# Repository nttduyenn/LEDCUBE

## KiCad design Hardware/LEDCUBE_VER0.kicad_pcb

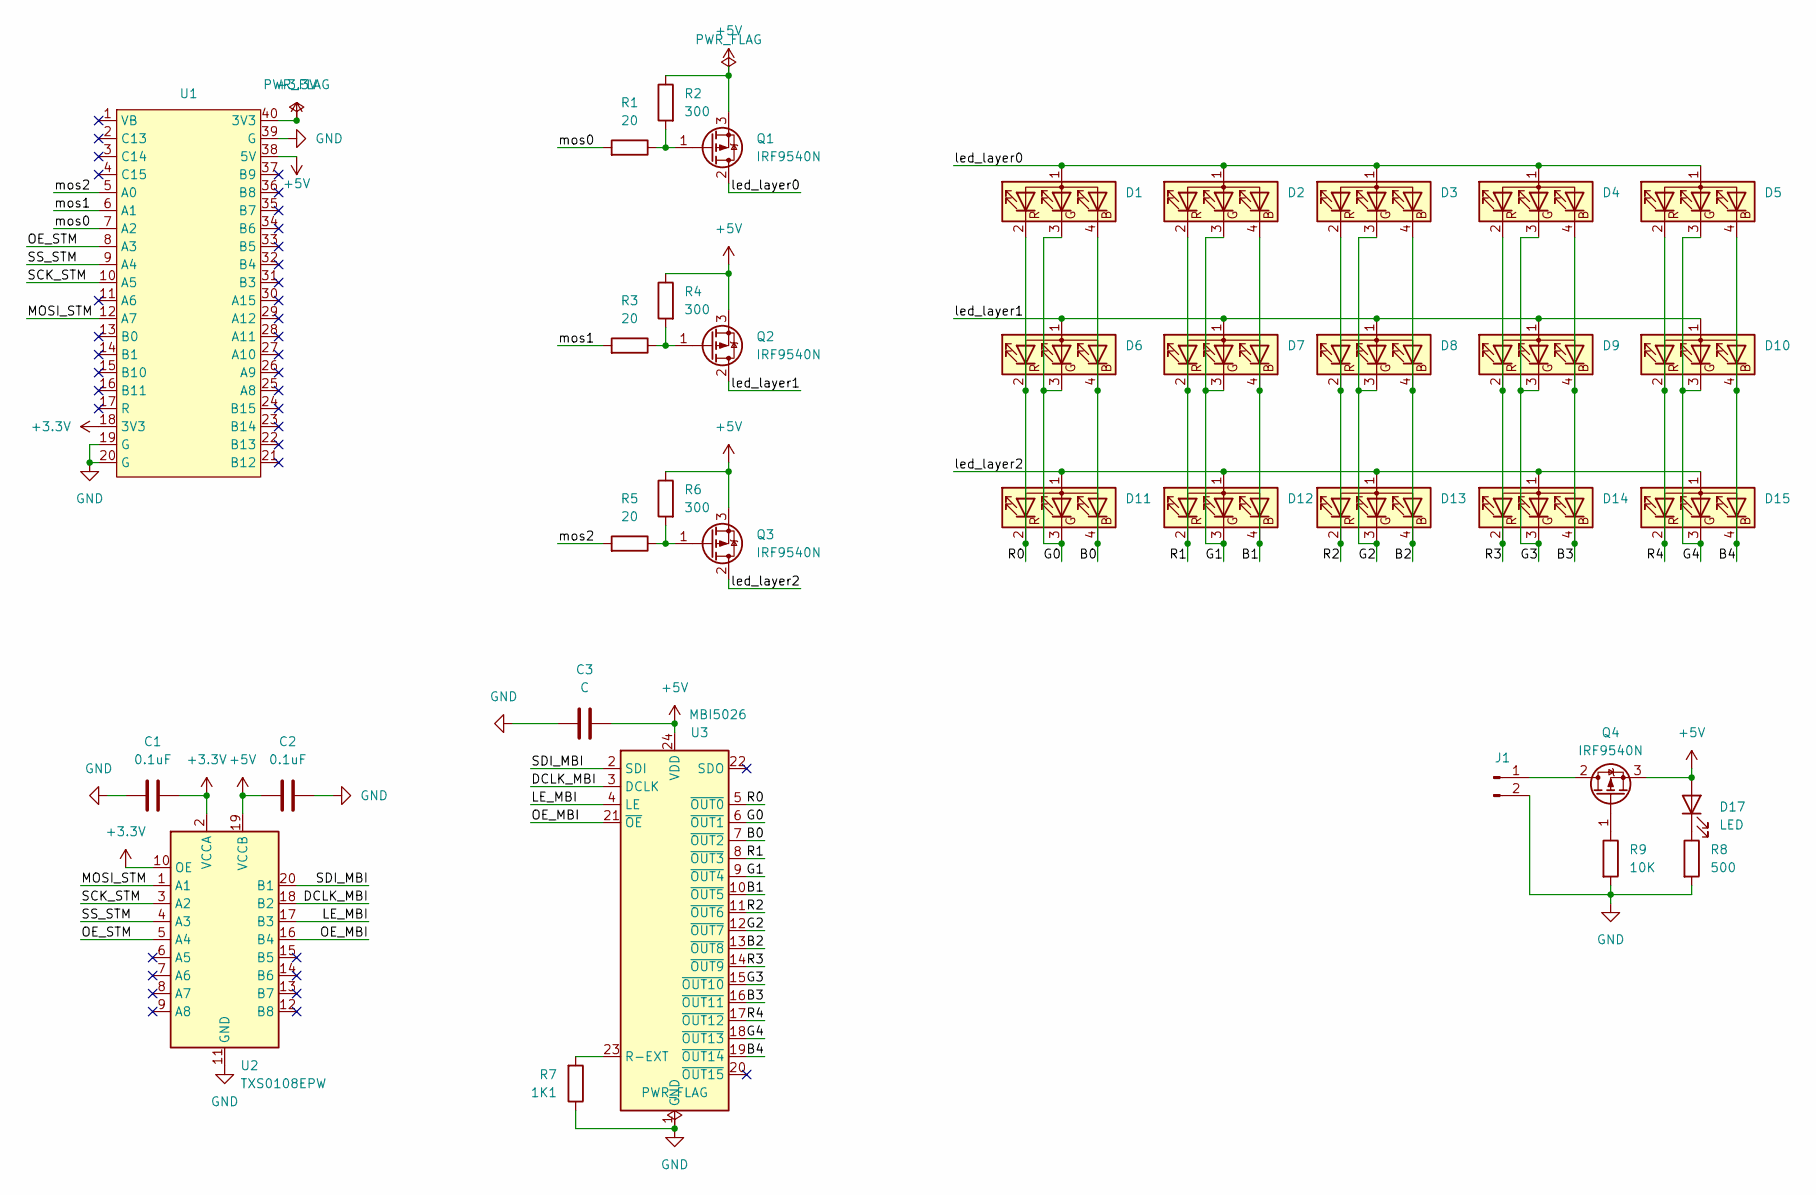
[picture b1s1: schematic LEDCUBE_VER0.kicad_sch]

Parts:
C1, C2: 0.1uF; C_0603_1608Metric_Pad1.08x0.95mm_HandSolder
C3: C; C_0805_2012Metric_Pad1.18x1.45mm_HandSolder
D1, D2, D3, D4, D5, D6, D7, D8, D9, D10, D11, D12, D13, D14, D15: LED_ARGB; LED_D5.0mm-4_RGB
D17: LED; D_0805_2012Metric_Pad1.15x1.40mm_HandSolder
J1: Conn_01x02_Pin; TerminalBlock_Phoenix_PT-1,5-2-5.0-H_1x02_P5.00mm_Horizontal
Q1, Q2, Q3, Q4: IRF9540N; TO-220-3_Vertical
R1, R3, R5: 20; R_0805_2012Metric_Pad1.20x1.40mm_HandSolder
R2, R4, R6: 300; R_0805_2012Metric_Pad1.20x1.40mm_HandSolder
R7: 1K1; R_0805_2012Metric_Pad1.20x1.40mm_HandSolder
R8: 500; D_0805_2012Metric_Pad1.15x1.40mm_HandSolder
R9: 10K; D_0805_2012Metric_Pad1.15x1.40mm_HandSolder
U1: STM32F1_BluePill
U2: TXS0108EPW; TSSOP-20_4.4x6.5mm_P0.65mm
U3: MBI5026; SOP-24

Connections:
+3.3V: C1.2, U1.18 (3V3), U1.40 (3V3), U2.2 (VCCA), U2.10 (OE)
+5V: C2.1, C3.2, D17.2 (A), Q1.3 (S), Q2.3 (S), Q3.3 (S), Q4.3 (S), R2.1, R4.1, R6.1, U1.38 (5V), U2.19 (VCCB), U3.24 (VDD)
/B0: D1.4 (BK), D6.4 (BK), D11.4 (BK), U3.7 (~OUT2)
/B1: D2.4 (BK), D7.4 (BK), D12.4 (BK), U3.10 (~OUT5)
/B2: D3.4 (BK), D8.4 (BK), D13.4 (BK), U3.13 (~OUT8)
/B3: D4.4 (BK), D9.4 (BK), D14.4 (BK), U3.16 (~OUT11)
/B4: D5.4 (BK), D10.4 (BK), D15.4 (BK), U3.19 (~OUT14)
/DCLK_MBI: U2.18 (B2), U3.3 (DCLK)
/G0: D1.3 (GK), D6.3 (GK), D11.3 (GK), U3.6 (~OUT1)
/G1: D2.3 (GK), D7.3 (GK), D12.3 (GK), U3.9 (~OUT4)
/G2: D3.3 (GK), D8.3 (GK), D13.3 (GK), U3.12 (~OUT7)
/G3: D4.3 (GK), D9.3 (GK), D14.3 (GK), U3.15 (~OUT10)
/G4: D5.3 (GK), D10.3 (GK), D15.3 (GK), U3.18 (~OUT13)
/LE_MBI: U2.17 (B3), U3.4 (LE)
/MOSI_STM: U1.12 (A7), U2.1 (A1)
/OE_MBI: U2.16 (B4), U3.21 (~OE)
/OE_STM: U1.8 (A3), U2.5 (A4)
/R0: D1.2 (RK), D6.2 (RK), D11.2 (RK), U3.5 (~OUT0)
/R1: D2.2 (RK), D7.2 (RK), D12.2 (RK), U3.8 (~OUT3)
/R2: D3.2 (RK), D8.2 (RK), D13.2 (RK), U3.11 (~OUT6)
/R3: D4.2 (RK), D9.2 (RK), D14.2 (RK), U3.14 (~OUT9)
/R4: D5.2 (RK), D10.2 (RK), D15.2 (RK), U3.17 (~OUT12)
/SCK_STM: U1.10 (A5), U2.3 (A2)
/SDI_MBI: U2.20 (B1), U3.2 (SDI)
/SS_STM: U1.9 (A4), U2.4 (A3)
/led_layer0: D1.1 (A), D2.1 (A), D3.1 (A), D4.1 (A), D5.1 (A), Q1.2 (D)
/led_layer1: D6.1 (A), D7.1 (A), D8.1 (A), D9.1 (A), D10.1 (A), Q2.2 (D)
/led_layer2: D11.1 (A), D12.1 (A), D13.1 (A), D14.1 (A), D15.1 (A), Q3.2 (D)
/mos0: R1.2, U1.7 (A2)
/mos1: R3.2, U1.6 (A1)
/mos2: R5.2, U1.5 (A0)
GND: C1.1, C2.2, C3.1, J1.2, R7.1, R8.2, R9.2, U1.19 (G), U1.20 (G), U1.39 (G), U2.11 (GND), U3.1 (GND)
unnamed: D17.1 (K), R8.1
unnamed: J1.1, Q4.2 (D)
unnamed: Q1.1 (G), R1.1, R2.2
unnamed: Q2.1 (G), R3.1, R4.2
unnamed: Q3.1 (G), R5.1, R6.2
unnamed: Q4.1 (G), R9.1
unnamed: R7.2, U3.23 (R-EXT)

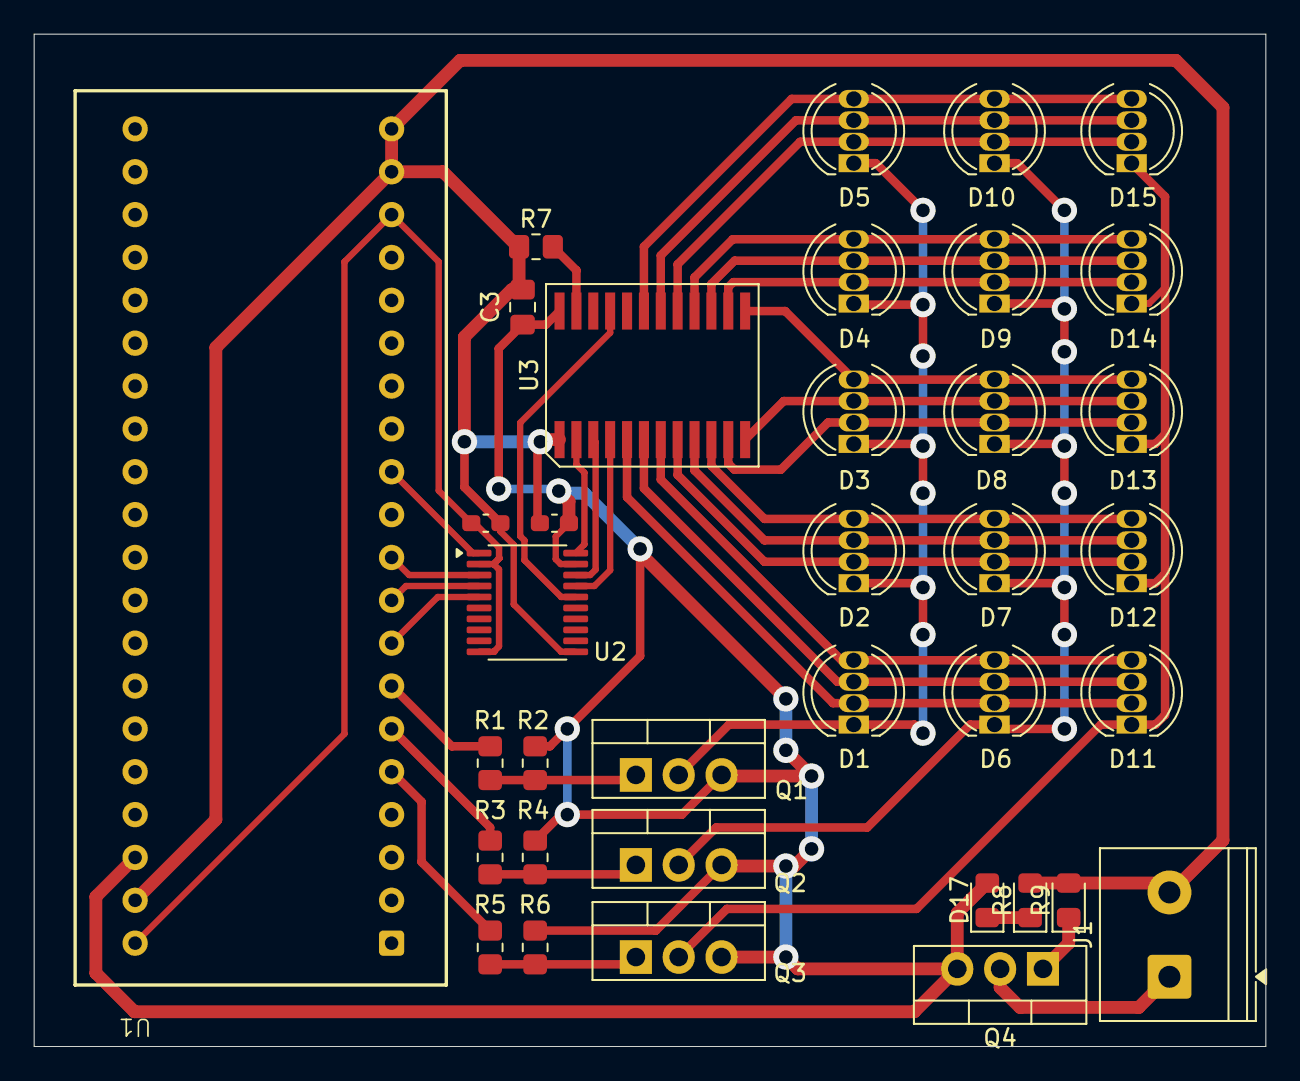
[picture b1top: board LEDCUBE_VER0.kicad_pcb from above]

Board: 2 copper layers, 73.0 x 60.0 mm, 36 parts (0 on the bottom side), 39 nets.
